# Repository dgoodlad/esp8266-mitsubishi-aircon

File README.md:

# ESP8266 / Mitsubishi AC interface

Software to control and monitor some Mitsubishi air conditioning units over MQTT
using an ESP8266-based wifi module.

Designed with the Adafruit HUZZAH breakout board in mind, this repo also
includes a PCB layout to do the requisite logic-level shifting etc.

**NOTE**: this information comes with _no warranty of any kind_. I do not claim
that any of the software or designs in this repository will work for your
particular hardware or situation. **MODIFYING AIR CONDITIONING UNITS IS
DANGEROUS AND YOU DO SO AT YOUR OWN RISK.***

## Supported Models

I haven't done any broad testing beyond the units in my own home. The underlying
library states that it has been

> Tested with Mitsubishi HeatPump MSZ-FH/GE (wall units) and SEZ-KD (ducted
> units)

and offers a wiki page listing its [Supported
Models](https://github.com/SwiCago/HeatPump/wiki/Supported-models). Check there
as a good place to start! Importantly, that page notes that

> if your unit has cn105 port, it is most likely supported

## Functional description

* Uses [WiFiManager](https://github.com/tzapu/WiFiManager/tree/development) for
  configuration via a captive portal access point
* GPIO12 acts as a "factory reset" button. When held low for 3 seconds, clears
  all settings configured by WiFiManager
* Uses the [HeatPump](https://github.com/SwiCago/HeatPump) library to handle
  comms with the aircon unit
* Uses [Async MQTT Client](https://github.com/marvinroger/async-mqtt-client) to
  communicate with your MQTT server. The messages are designed to line up with
  the expectations of the [Home Assistant](https://www.home-assistant.io/) [MQTT
  HVAC component](https://www.home-assistant.io/components/climate.mqtt/).
* Detects the presence of the aircon unit (rather than USB/FTDI/debug power) by
  looking for a high signal on GPIO4. The PCB implements this using a voltage
  divider to step the 5V power supply down to 3V3.
* If an aircon unit is detected:
    * Calls `Serial.swap()` to make UART0 use GPIO13/15 as RX/TX for the aircon
      serial communication. This avoids connecting the aircon to the default
      RX/TX pins that dump some debug/boot-time information from the ESP8266
      chip
    * Uses `Serial1` (UART1) to output debug logs on GPIO2 at 115200/8N1
* If _no_ aircon unit is detected
    * The heatpump code does not start, and no call to `Serial.swap()` is made.
    * Uses `Serial` (UART0) to output debug logs on GPIO1 (TX) at 115200/8N1
    * `Serial1` (UART1) is *not used*

## PCB

I used [OSH Park](https://oshpark.com/) to fabricate these PCBs, it cost about
10 USD with free shipping to 🇦🇺Australia🇦🇺 for three boards. I've made a shared
project there if you'd like to order the boards quickly: 

Note that the HUZZAH is **revA** with _11 pin connectors_, not the newer 10-pin
version. The 11-pin version is just what I had a few of lying around, and they
have an extra no-connection (NC) pin between the power and GPIO pins on each
row. The order of the pins is _exactly the same_ and it would be straightforward
to modify the board layout to use the newer 10-pin version instead.

### Bill of Materials

You'll need the following to build the PCB:

| Reference(s) | Qty   | Value       | Description                                 | Datasheet                                                           | Digikey Part Number                                                                                                             | RS Components P/N                                                                          |
| ------------ | ----- | ----------- | -----------                                 | ---------                                                           | --------------------                                                                                                            | --------------------                                                                       |
| A1           | 1     | HUZZAH      | Adafruit HUZZAH (revA) breakout             | [link](https://learn.adafruit.com/adafruit-huzzah-esp8266-breakout) | [1528-1223-ND](https://www.digikey.com.au/product-detail/en/adafruit-industries-llc/2471/1528-1223-ND/5355489)                  |                                                                                            |
| C1, C2       | 2     | 0.1uF       | SMD 0603 Ceramic Capacitor                  | [link]()                                                            | [1276-6994-1-ND](https://www.digikey.com.au/product-detail/en/samsung-electro-mechanics/CL10B104KB85PNL/1276-6994-1-ND/7320636) |                                                                                            |
| J1           | 1     | AIRCON      | JST PH 4-pin Male Connector                 | [link](http://www.jst-mfg.com/product/pdf/eng/ePH.pdf)              | [455-1721-ND](https://www.digikey.com.au/product-detail/en/jst-sales-america-inc/S4B-PH-K-S(LF)(SN)/455-1721-ND/926628)         |                                                                                            |
| J2           | 1     | DEBUG       | 2-pin 0.1" pin header (male)                | [link]()                                                            | [S7000-ND](https://www.digikey.com.au/product-detail/en/sullins-connector-solutions/PPTC021LFBN-RC/S7000-ND/810142)             |                                                                                            |
| n/a          | 2     | 11-PIN      | 11-pin 0.1" pin header (female)             | [link]()                                                            | [S7009-ND](https://www.digikey.com.au/product-detail/en/sullins-connector-solutions/PPTC111LFBN-RC/S7009-ND/810150)             |                                                                                            |
| R1           | 1     | 2K2         | SMD 0603 Resistor                           | [link]()                                                            |                                                                                                                                 | [679-0112](https://au.rs-online.com/web/p/surface-mount-fixed-resistors/6790112/?sra=pstk) |
| R2           | 1     | 3K3         | SMD 0603 Resistor                           | [link]()                                                            |                                                                                                                                 | [679-0311](https://au.rs-online.com/web/p/surface-mount-fixed-resistors/6790311/?sra=pstk) |
| R3, R4       | 2     | 1K          | SMD 0603 Resistor                           | [link]()                                                            |                                                                                                                                 | [678-9875](https://au.rs-online.com/web/p/surface-mount-fixed-resistors/6789875/?sra=pstk) |
| SW1          | 1     | KMR2        | SMD tactile push-button switch              | [link](https://www.ckswitches.com/media/1479/kmr2.pdf)              |                                                                                                                                 | [135-9490](https://au.rs-online.com/web/p/tactile-switches/1359490/)                       |
| U1           | 1     | TXB0104DR   | 4-channel logic level shifter, SOIC package | [link](http://www.ti.com/lit/ds/symlink/txb0104.pdf)                | [296-21928-1-ND](https://www.digikey.com.au/product-detail/en/texas-instruments/TXB0104DR/296-21928-1-ND/1629281)               |                                                                                            |

You should be able to pick these parts up for under AUD25, but YMMV. I've linked
to the vendors that I used (Digikey & RS Components) in Australia. I used two
sources because I was ordering parts as I experimented, and RS does free
shipping within Australia on _any order size_ while Digikey requires a minimum
order value. None of these parts are particularly special, and you should be
fine swapping out resistors, caps etc so long as you keep the values (especially
for the voltage divider R1/R2).

I created a BOM at Digikey with pricing as of 3/1/2019 and have exported it as
CSV [here](docs/bom-digikey.csv?raw=true). It contains everything you need to
build the PCB and a cable (except for wire!).

### Cabling

To connect the PCB to your air conditioner, you need to make an appropriate
cable.

On the aircon end, they use a [JST
PA-series](http://www.jst-mfg.com/product/pdf/eng/ePA-F.pdf) 5-conductor
connector, of which we only need four (pin 1 is a +12V output that is
unnecessary here).

On the PCB, I've used a [JST
PH-series](http://www.jst-mfg.com/product/pdf/eng/ePH.pdf) 4-conductor
connector. 

You'll need the following parts to build a cable:

| JST Part Number | Qty | Description                             | Notes                        | AU RS Components URL                                           |
| -----------     | --- | -----------                             | -----                        | --------------------                                           |
| SPHD-002T-0.5   | 4   | PA-series crimp connector               | BPHD-002T-0.5 is equivalent  | https://au.rs-online.com/web/p/pcb-connector-contacts/9182817/ |
| PAP-05V-S       | 1   | PA-series connector housing (5-circuit) |                              | https://au.rs-online.com/web/p/pcb-connector-housings/4766798/ |
| SPH-002T-P0.5S  | 4   | PH-series crimp connector               | BPH-002T-P0.5S is equivalent | https://au.rs-online.com/web/p/pcb-connector-contacts/8201456/ |
| PHR-4           | 1   | PH-series connector housing (4-circuit) |                              | https://au.rs-online.com/web/p/pcb-connector-housings/8201478/ |

... and four wires (or a 4-core cable) that meet the requirements of both crimp
connectors. That means anything 28-24 AWG, with insulation outside diameter
between 0.8mm-1.5mm.

Note that the crimp connectors _may_ be offered in a `B`-prefixed part number
instead of `S`; they'll be fine, too, they're just packaged as individual parts
in bags rather than on a long metal strip.

I used an Engineer PA-09 crimper for these connectors. They're small and
finnicky but once you get the hang of it they're do-able. Some vendors sell
pre-crimped leads if you want to skip crimping (at least on one end). If I
re-design the board in the future, I'd put a PA connector on that end for
consistency and for availability of pre-made leads.

The wiring is simple, as I've kept the pin order from the aircon unit:

``` text
    Aircon                      PCB
Signal | Pin                 Pin | Signal
   12V | 1 * (NC)
   GND | 2 * ----------------* 1 | GND
    5V | 3 * ----------------* 2 | 5V
    TX | 4 * ----------------* 3 | RX
    RX | 5 * ----------------* 4 | TX
```

For convenience, here are the diagrams of the two connector housings from their
respective datasheets:

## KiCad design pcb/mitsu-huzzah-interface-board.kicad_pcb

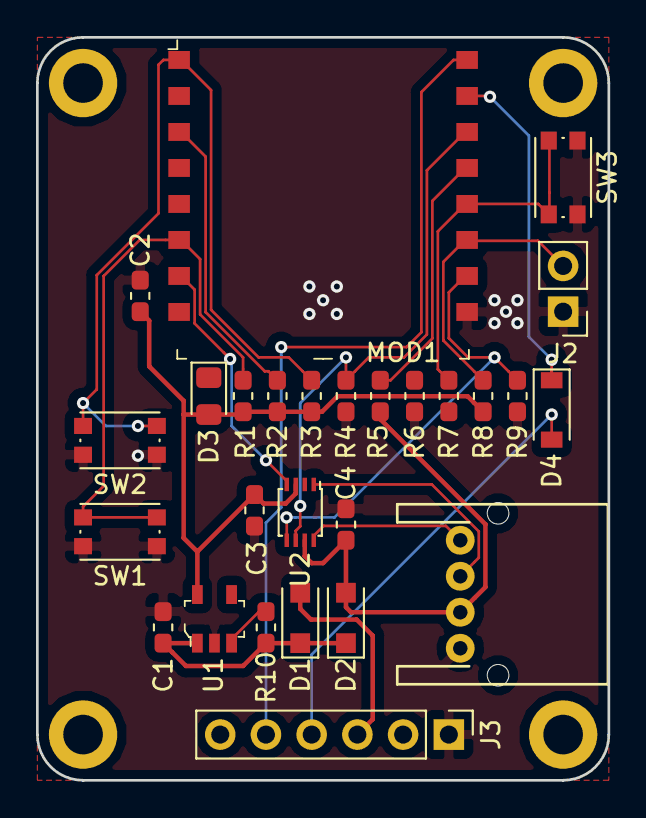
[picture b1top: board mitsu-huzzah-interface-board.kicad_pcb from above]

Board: 2 copper layers, 31.8 x 41.3 mm, 27 parts (0 on the bottom side), 21 nets.

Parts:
C1, C2: 10uF; C_0603_1608Metric_Pad1.05x0.95mm_HandSolder
C3, C4: 0.1uF; C_0603_1608Metric_Pad1.05x0.95mm_HandSolder
D1, D2: MBR120; D_SOD-123F
D3: RED; LED_0805_2012Metric_Pad1.15x1.40mm_HandSolder
D4: MMSD914; D_SOD-123
J1: AIRCON; S04B-PASK-2
J2: DEBUG; PinHeader_1x02_P2.54mm_Vertical
J3: FTDI; PinHeader_1x06_P2.54mm_Vertical
MOD1: 2491; WIFI_Module_ESP8266_2491
R1, R2, R3, R4, R8, R9, R10: 10K; R_0603_1608Metric_Pad1.05x0.95mm_HandSolder
R5: 2K2; R_0603_1608Metric_Pad1.05x0.95mm_HandSolder
R6: 3K3; R_0603_1608Metric_Pad1.05x0.95mm_HandSolder
R7: 1K; R_0603_1608Metric_Pad1.05x0.95mm_HandSolder
SW1, SW2, SW3: KMR2; SW_SPST_KMR2
U1: AP2112K-3.3TRG1; SOT-753
U2: TXB0102DCU; VSSOP-8_2.4x2.1mm_P0.5mm

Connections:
+3V3: C2.1, C3.1, D3.2, MOD1.8, R1.1, R2.1, R3.1, R8.1, U1.5, U2.3
+5V: C4.1, D2.2, J1.2, R5.1, U2.7
/5V_DET: MOD1.13, R5.2, R6.1
/CH_PD: MOD1.3, R2.2
/CLEAR: MOD1.6, R1.2, SW1.2
/FTDI_5V: D1.2, J3.3
/FTDI_RX: J3.5, MOD1.16
/FTDI_TX: D4.2, J3.4
/GPIO0: MOD1.12, R7.2, SW3.2
/GPIO2: J2.2, MOD1.11, R8.2
/GPIO13: MOD1.7, U2.4
/GPIO15: MOD1.10, R9.1, U2.5
/OE: MOD1.14, R4.1, U2.6
/RESET: MOD1.1, R3.2, SW2.2
/RXD0: D4.1, MOD1.15
/RXD0*_5V: J1.3, U2.1
/TXD0*_5V: J1.4, U2.8
GND: C1.2, C2.2, C3.2, C4.2, J1.1, J2.1, J3.1, MOD1.9, R4.2, R6.2, R9.2, SW1.1, SW2.1, SW3.1, U1.2, U2.2
unnamed: C1.1, D1.1, D2.1, R10.1, U1.1
unnamed: D3.1, R7.1
unnamed: R10.2, U1.3

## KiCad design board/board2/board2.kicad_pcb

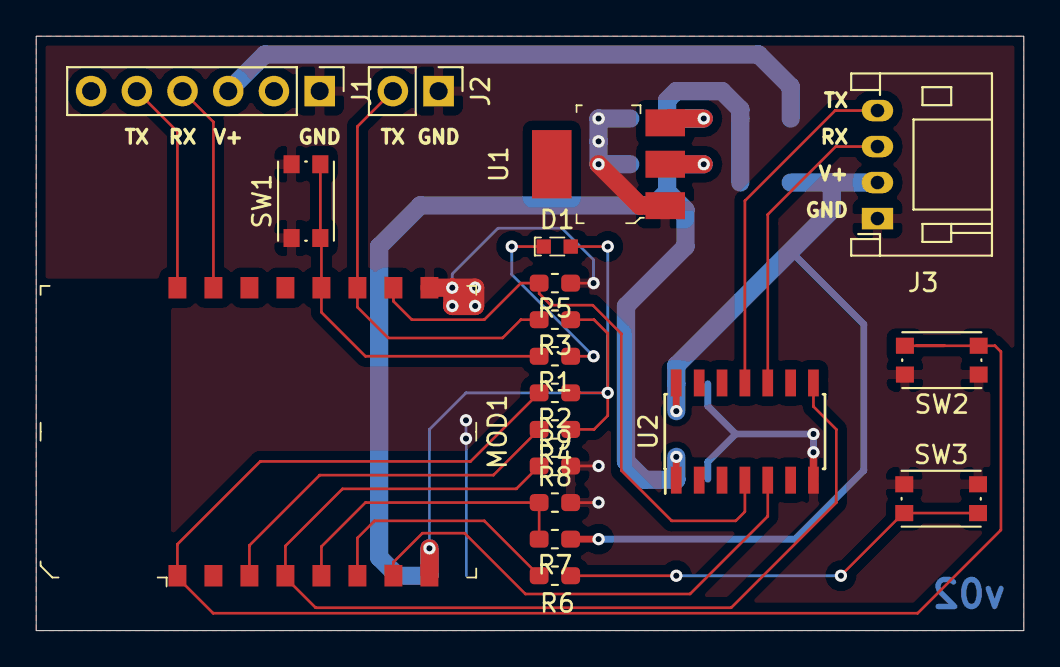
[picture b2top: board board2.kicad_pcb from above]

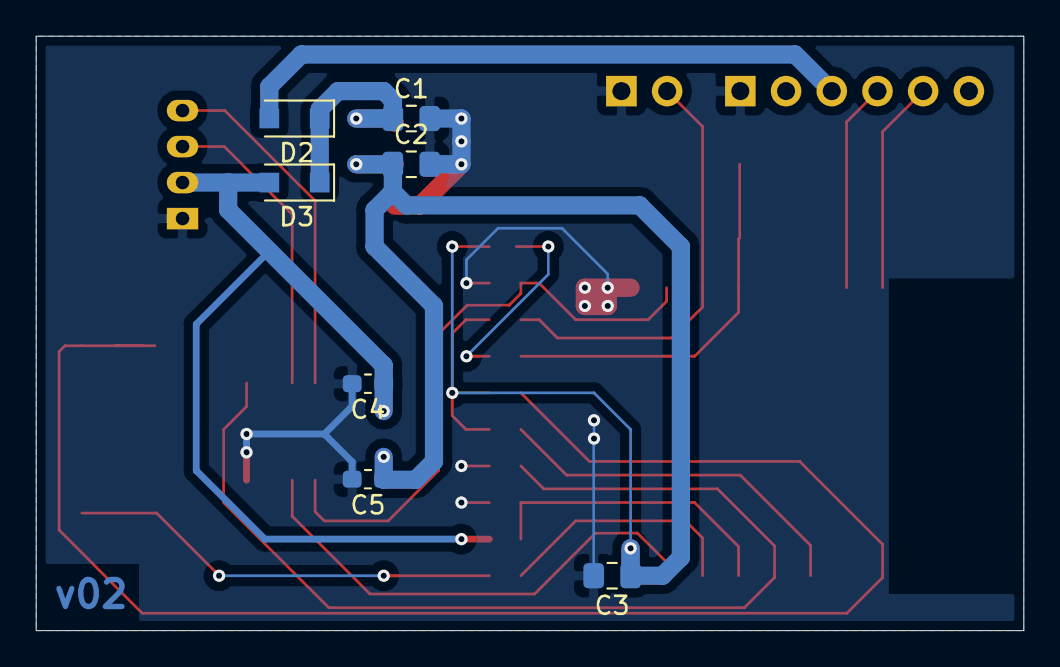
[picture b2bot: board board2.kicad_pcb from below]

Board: 2 copper layers, 54.9 x 33.0 mm, 26 parts (7 on the bottom side), 20 nets.

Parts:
C1, C2, C3: 10uF; C_0805_2012Metric_Pad1.15x1.40mm_HandSolder
C4, C5: 0.1uF; C_0603_1608Metric_Pad1.05x0.95mm_HandSolder
D1: RED; LED_2-SMD_No_Lead_1.7x0.8mm
D2, D3: D_Schottky; D_SOD-123F
J1: FTDI; PinHeader_1x06_P2.54mm_Vertical
J2: DEBUG; PinHeader_1x02_P2.54mm_Vertical
J3: MITSU_AC; JST_PH_S4B-PH-K_1x04_P2.00mm_Horizontal
MOD1: ESP-12S; WIFI_Module_ESP8266_2491
R1: 1K; R_0603_1608Metric_Pad1.05x0.95mm_HandSolder
R2, R3, R4, R5, R6, R9: 10K; R_0603_1608Metric_Pad1.05x0.95mm_HandSolder
R7: 1K8; R_0603_1608Metric_Pad1.05x0.95mm_HandSolder
R8: 3K3; R_0603_1608Metric_Pad1.05x0.95mm_HandSolder
SW1, SW2, SW3: SW_Push; SW_SPST_KMR2
U1: AP2114H-3_3TRG1; SOT-223
U2: TXB0104D; SOIC-14_3.9x8.7mm_P1.27mm

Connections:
+3V3: C2.1, C3.1, C5.1, D1.2, MOD1.8, R2.1, R3.1, R4.1, U1.2, U2.1
/CH_PD: MOD1.3, R4.2
/GPIO0: MOD1.12, R1.2, SW1.2
/GPIO2: J2.2, MOD1.11, R3.2
/GPIO12: MOD1.6, R6.1
/GPIO13: MOD1.7, U2.5
/GPIO14: MOD1.5, R7.2, R8.1
/GPIO15: MOD1.10, R5.1, U2.4
/GPIO16: MOD1.4, R9.1, U2.8
/RESET: MOD1.1, R2.2, SW2.2
/RX0: J1.4, MOD1.15
/RX0*_5V: J3.3, U2.10
/TX0: J1.5, MOD1.16
/TX0*_5V: J3.4, U2.11
GND: C1.2, C2.2, C3.2, C4.2, C5.2, J1.1, J2.1, J3.1, MOD1.9, R5.2, R8.2, R9.2, SW1.1, SW2.1, SW3.1, U1.1, U2.7
unnamed: D1.1, R1.1
unnamed: R6.2, SW3.2
VBUS: C4.1, D3.2, J3.2, R7.1, U2.14
VCC: C1.1, D2.1, D3.1, U1.3
VPP: D2.2, J1.3

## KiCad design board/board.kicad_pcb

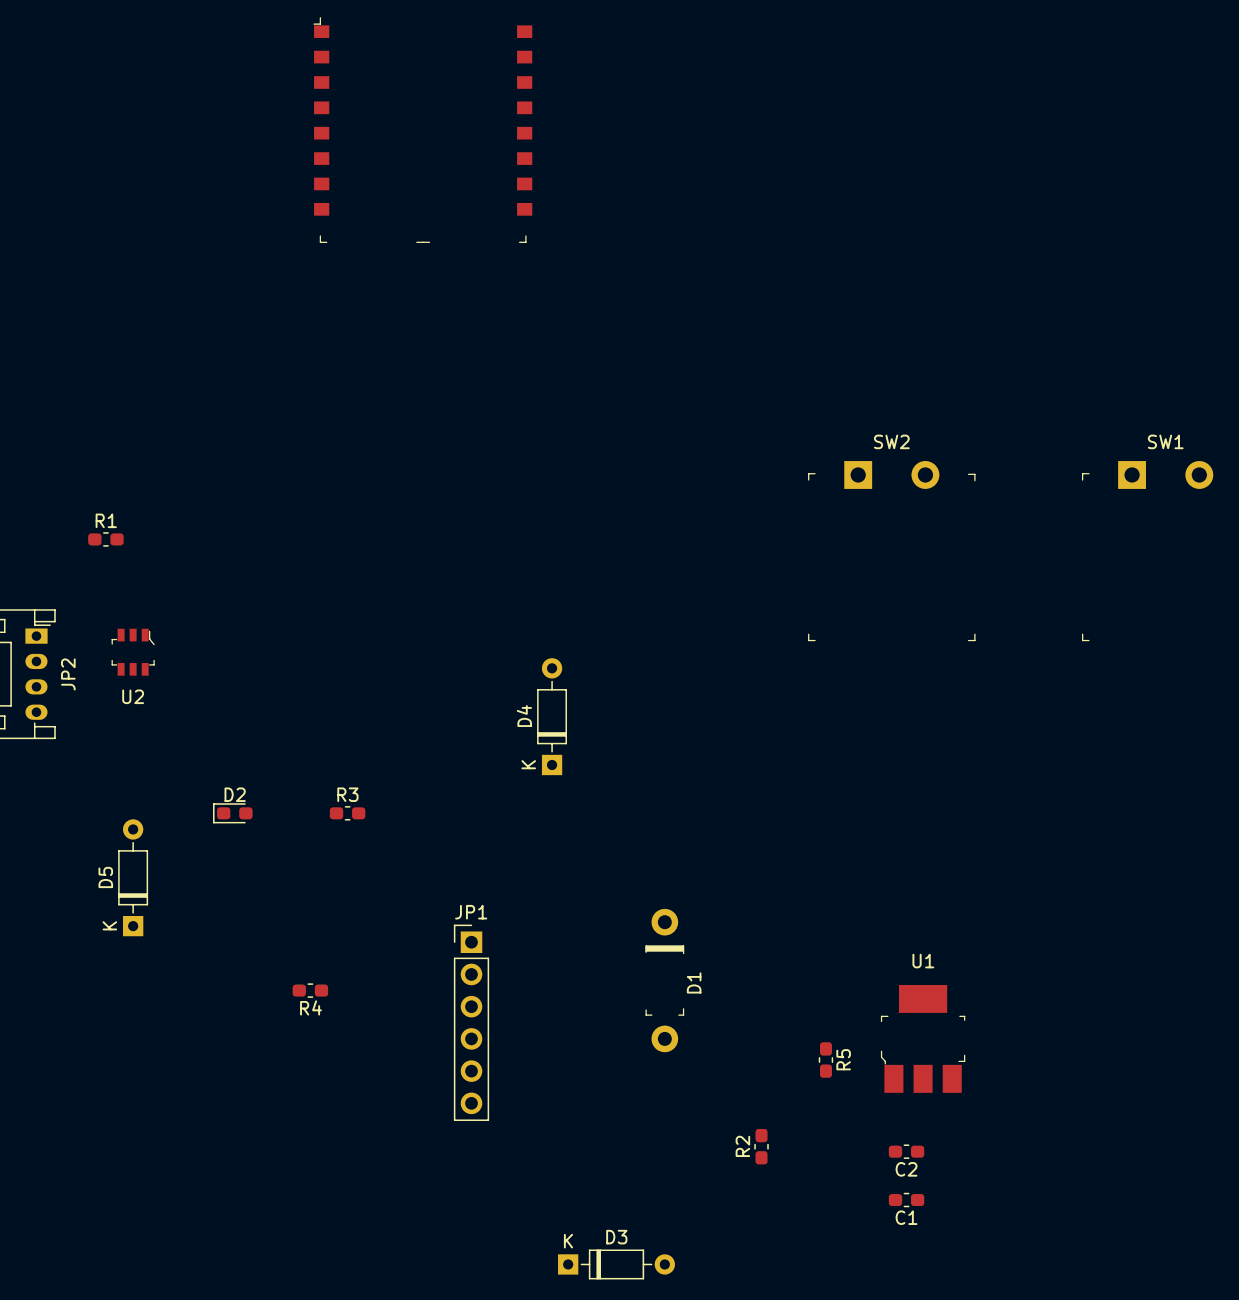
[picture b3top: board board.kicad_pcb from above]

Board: 2 copper layers, 19 parts (0 on the bottom side), 16 nets, no tracks yet.

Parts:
C1, C2: 4.7uF; C_0603_1608Metric_Pad1.05x0.95mm_HandSolder
D1: 1N5817; DO-41
D2: LED; LED_0603_1608Metric_Pad1.05x0.95mm_HandSolder
D3, D4, D5: 1N4148; D_DO-35_SOD27_P7.62mm_Horizontal
JP1: FTDI; PinHeader_1x06_P2.54mm_Vertical
JP2: MITSU AC; JST_PH_S4B-PH-K_1x04_P2.00mm_Horizontal
MOD1: ESP12S; WIFI_Module_ESP8266_2491
R1: 1K; R_0603_1608Metric_Pad1.05x0.95mm_HandSolder
R2, R3, R4, R5: 10K; R_0603_1608Metric_Pad1.05x0.95mm_HandSolder
SW1, SW2: GPTS203211B; PushButton_12x12mm_THT_GPTS203211B
U1: AP2114H; SOT-223
U2: SN74LVC1T45; SOT-23-6

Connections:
+3V3: C2.1, D2.2, MOD1.8, R2.1, R3.1, R4.1, U1.2, U2.6
+5V: D1.A, JP1.4, JP2.3, U2.1
/CH_PD: MOD1.3, R4.2
/GPIO0: MOD1.12, R1.2, SW1.2
/GPIO2: MOD1.11, R3.2
/GPIO13: D5.2, MOD1.7
/GPIO15: MOD1.10, R5.1, U2.4
/RESET: D3.2, MOD1.1, R2.2, SW2.2
/RX0: D4.2, MOD1.15
/RX0*_5V: D5.1, JP2.2
/RX0_5V: D4.1, JP1.3
/TX0: JP1.2, MOD1.16
/TX0*_5V: JP2.1, U2.3
GND: C1.2, C2.2, JP1.6, JP2.4, MOD1.9, R5.2, SW1.1, SW2.1, U1.1, U2.2, U2.5
unnamed: C1.1, D1.K, U1.3
unnamed: D2.1, R1.1

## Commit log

2018-08-15 platformio init
2018-08-16 Create CaptivePortal (thanks @madpilot)
2018-08-16 Ignores
2018-08-16 Fire up the captive portal
2018-08-16 Remove unused variable
2018-08-16 Fix dependency name
2018-08-16 Add notfound handler to captive portal
2018-08-19 Captive portal and config server working
2018-08-19 Cheesy copypasta from madpilot/felux-config
2018-08-23 Minor config app tweaks
2018-11-26 initial import
2018-11-26 Use WifiManager custom params example as a base
2018-11-26 Ignore vscode
2018-12-01 Ignore clang_complete
2018-12-02 Fix dependencies
2018-12-02 Set the config AP name based on chipid
2018-12-02 Vendor SwiCago/Heatpump
2018-12-02 Initialise the MQTT client
2018-12-02 Quickly tie mqtt/heatpump status/settings together
2018-12-02 Handle incoming commands via mqtt
2018-12-02 Enable the heatpump code I guess!
2018-12-02 Subscribe to the mqtt command topics
2018-12-05 Add a pcb
2018-12-11 Start refactoring with development WiFiManager lib
2018-12-11 Reset settings by holding button for 3 seconds
2018-12-12 Validate incoming values
2018-12-12 Up-case any incoming payloads for simplicity
2018-12-16 Build a much better PCB
2018-12-16 Commit the old board changes for posterity
2018-12-16 Write up a README
2018-12-16 Detect the heatpump on pin 4
2018-12-16 Enable the logic level shifter
2018-12-16 Use the right pin (not pin number, GPIO number)
2018-12-16 Don't try and pullup the pin internally
2018-12-16 Print WM debug info properly among other things
2018-12-16 Add a disclaimer
2018-12-16 Add a script to monitor and hexdump heatpump uart
2018-12-17 Fix handling of the mqtt client's payload buffers
    The `char* payload` buffer given to the onMessage callback is the raw
    TCP buffer, and not a null-terminated string as I'd expected. While we
    can technically receive payloads larger than the tcp window, we know
    that all valid payloads will be 6 characters or less so we don't bother
    checking `index` and `total`, and just blindly use the `len`.
    The `upcase` function is now pretty specific to this situation, so it'll
2018-12-17 Upload at 115200 baud for stability
2018-12-17 Print single bytes
2018-12-17 Let the HeatPump class call Serial.swap()
    I'm settling on leaving this library's behaviour as unchanged as
    possible, and to just allow it to optionally call swap for us rather
    than changing things to accept an already-configured serial object or
    something: too much effort.
2018-12-17 Fix warning about signed/unsigned comparisons
2018-12-17 Update the README
2018-12-17 Add the bill-of-materials CSV from kicad
2018-12-17 Update the PCB with a bigger level shifter
2018-12-17 MIT License
    Do what you want with this software, but I don't warrant anything about
    it.
2018-12-17 Publish node availability using last-will mqtt
2018-12-17 Send "OFF" as the mode payload if power is off
2018-12-17 Add an example mqtt configuration
2018-12-17 Move the HeatPump library to the lib folder
2018-12-17 Note about supported models
2018-12-18 Update voltage divider resistor values
    2K2/3K3 gives a 3V output too, and I didn't want to wait for stock on
    the old values.
2018-12-18 Update the rendered pcb stuff
2018-12-18 SVGs can't be linked "raw"
2018-12-18 Update the BOM
2018-12-22 Add OTA updates
2018-12-31 Ensure repeated packets are printed
2018-12-31 Persist the pin-swapping behavior
2018-12-31 :fire: String, use const char* instead
2018-12-31 Debug packet data
2018-12-31 First implementation for hardware v01
2018-12-31 Print system info on boot and every 60 seconds
2018-12-31 Fix crash on settings change
    I was erroneously executing heatpump::update inside the mqtt message
    handler, which caused a software watchdog reset because the serial comms
    are too slow. Instead I now do the right thing and batch updates to
    happen during the main arduino loop function 500ms after the last update
    was received.
2018-12-31 Print fatal exception details
2018-12-31 Working home assistant configuration
2018-12-31 Remove pre-production note and add qty to BOM
2018-12-31 Fix table
2019-01-03 Be more explicit about WiFiManager config
2019-01-03 Conditionally print packet dumps
2019-01-03 Write HIGH to GPIO12 on hardware v01
2019-01-03 Update documentation
2019-01-03 Fill in links to buy all the parts
2019-01-03 fixup! Fill in links to buy all the parts
2019-01-03 Add digikey BOM
2019-01-03 Hardware v01 doesn't have a clear settings button
2019-01-21 Enable syslog logging all over the place
2019-01-21 Load syslog configs from SPIFFS json
2019-01-26 Fix clear-settings button
    Set it as a pullup input, because in its "no button pressed" state the
    pin is left floating on hardware v02.
2019-01-26 Use a static json buffer to reduce RAM usage
2019-01-26 Fix syslog log level setting tests
2019-01-26 Change the default port for MQTT to 1883
2019-01-27 Use HeapPump library via platformio libdeps
    For now reference my branch in SwiCago/HeatPump#101 but once it's merged
    we can switch to upstream proper.
2019-01-27 Change design to a completely custom PCB
    No more adafruit HUZZAH, instead build a custom PCB for an ESP-12S module.
